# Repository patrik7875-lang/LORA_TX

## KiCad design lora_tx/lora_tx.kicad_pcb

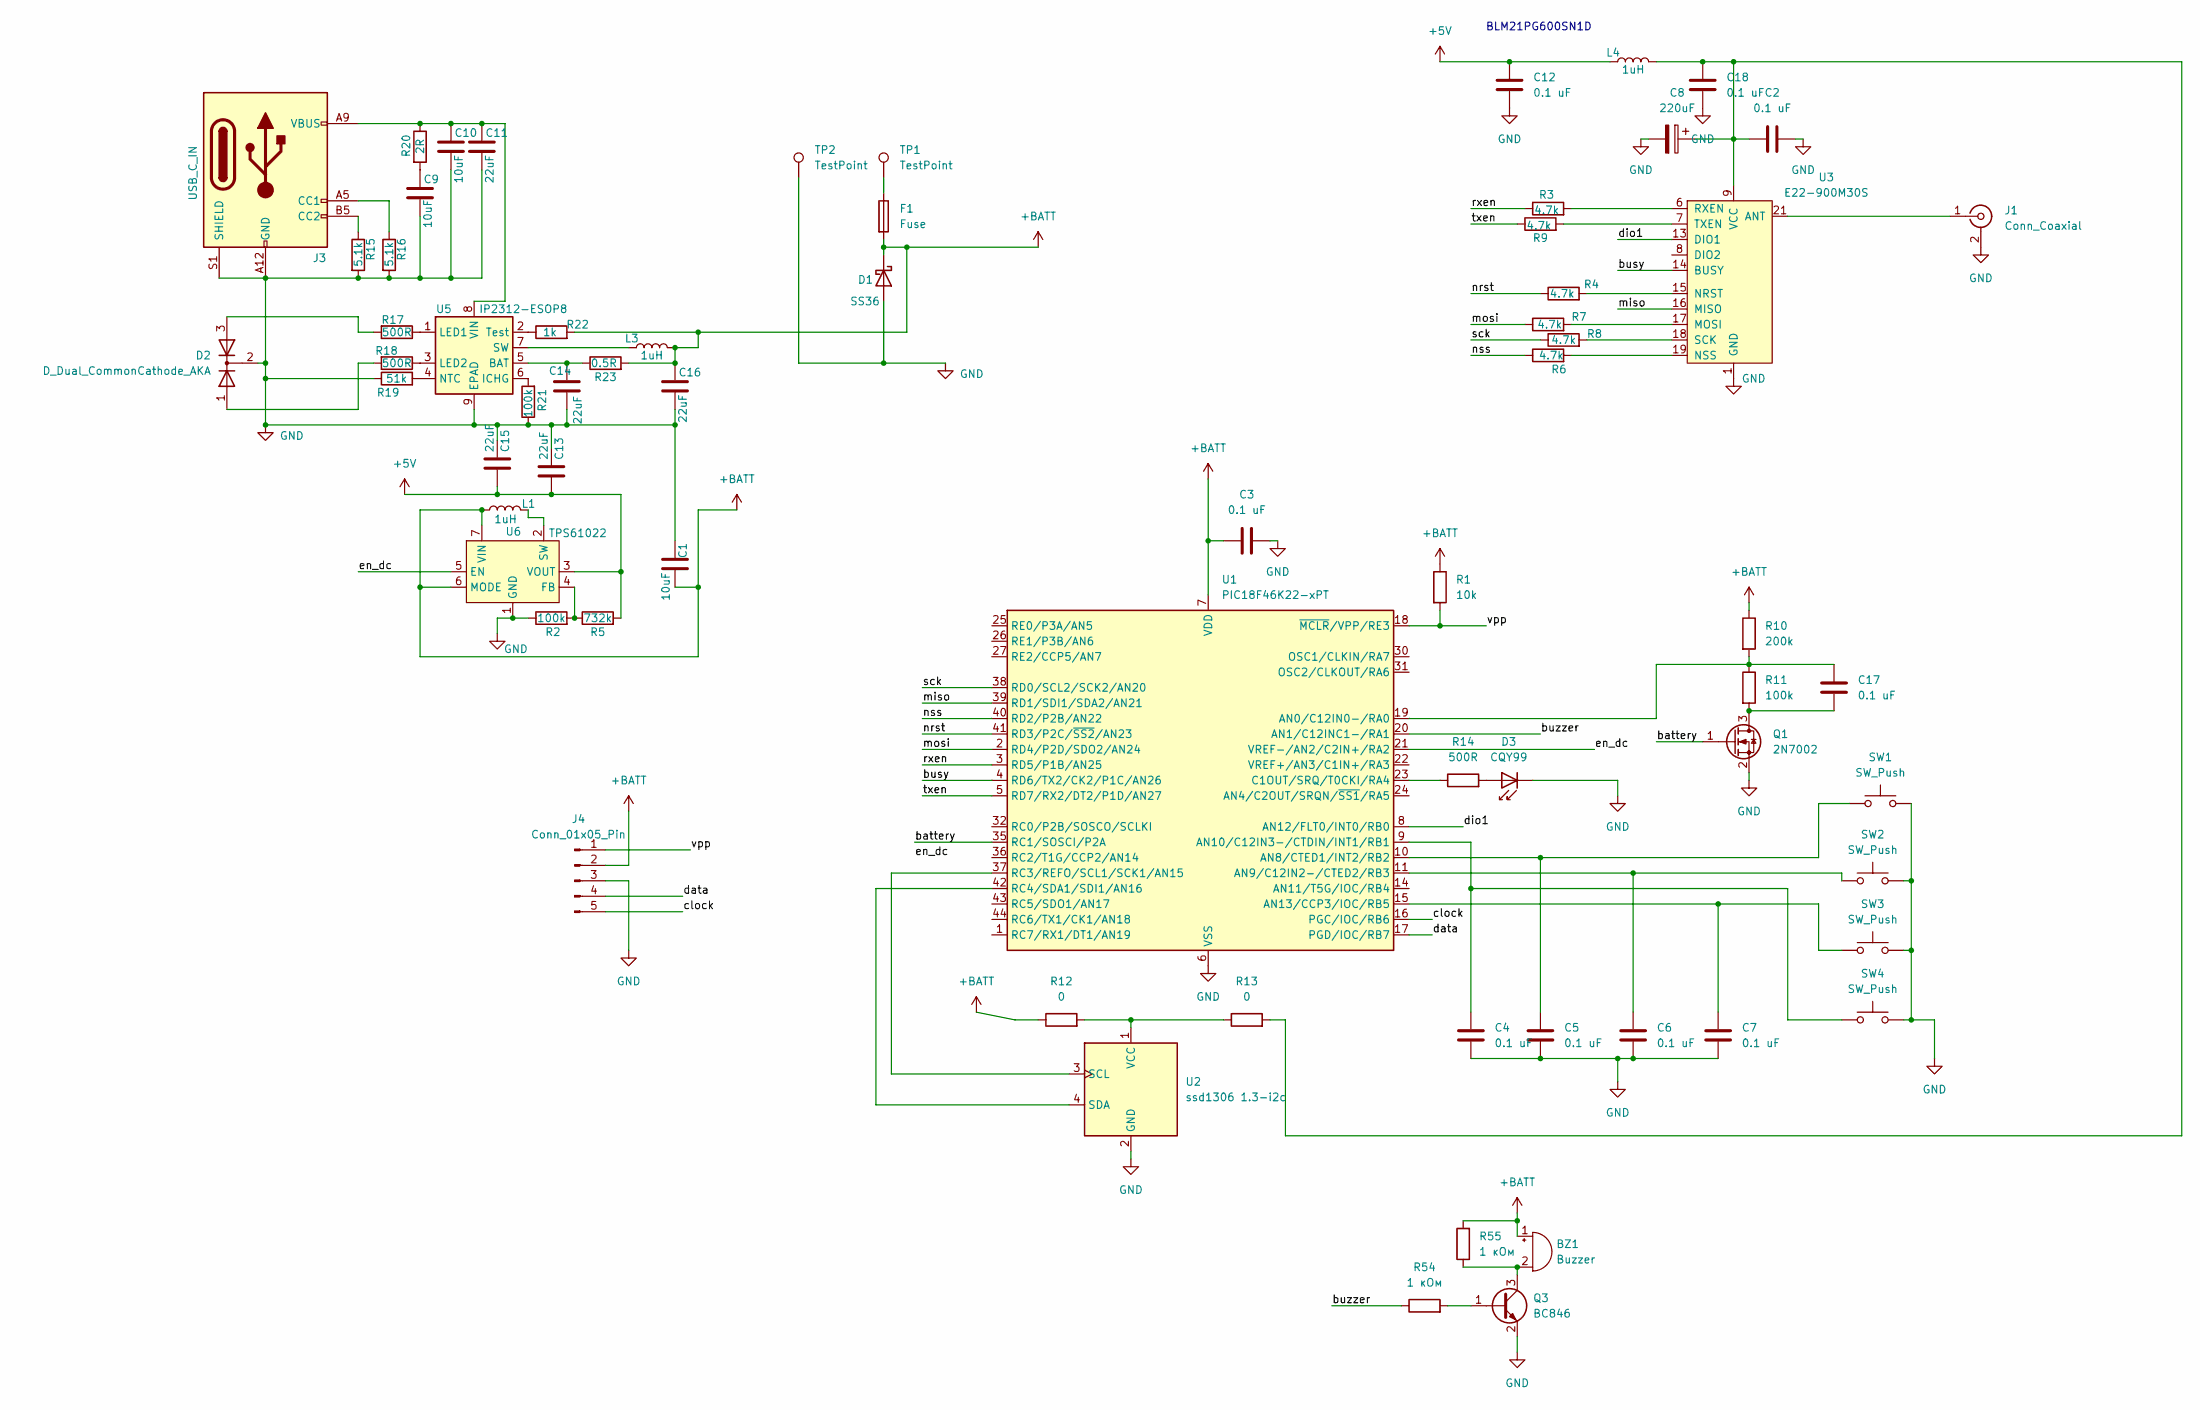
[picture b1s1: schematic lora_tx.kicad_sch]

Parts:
BZ1: Buzzer; Buzzer_Murata_PKMCS0909E
C1, C9, C10: 10uF; C_0805_2012Metric_Pad1.18x1.45mm_HandSolder
C2, C3, C12, C17, C18: 0.1 uF; LED_0805_2012Metric
C4, C5, C6, C7: 0.1 uF; C_0805_2012Metric
C8: 220uF; CP_EIA-7343-31_Kemet-D
C11, C13, C14, C15, C16: 22uF; C_1206_3216Metric
D1: SS36; D_SMA
D2: D_Dual_CommonCathode_AKA; LED_D3.0mm-3
D3: CQY99; LED_D1.8mm_W1.8mm_H2.4mm_Horizontal_O1.27mm_Z8.2mm
F1: Fuse; Fuse_1210_3225Metric
J1: Conn_Coaxial; SMA_Molex_73251-1153_EdgeMount_Horizontal
J3: USB_C_IN; USB_C_Receptacle_GCT_USB4125-xx-x_6P_TopMnt_Horizontal
J4: Conn_01x05_Pin; PinHeader_1x05_P2.54mm_Vertical
L1, L3: 1uH; L_Chilisin_BMRA00050520
L4: 1uH; L_0805_2012Metric
Q1: 2N7002; SOT-23
Q3: BC846; SOT-23
R1: 10k; R_0805_2012Metric
R2, R21: 100k; R_0805_2012Metric_Pad1.20x1.40mm_HandSolder
R3, R4, R6, R7, R8, R9: 4.7k; R_0805_2012Metric
R5: 732k; R_0805_2012Metric_Pad1.20x1.40mm_HandSolder
R10: 200k; R_0805_2012Metric
R11: 100k; R_0805_2012Metric
R12, R13: 0; R_1206_3216Metric
R14: 500R; R_0805_2012Metric
R15, R16: 5.1k; R_0805_2012Metric_Pad1.20x1.40mm_HandSolder
R17, R18: 500R; R_0805_2012Metric_Pad1.20x1.40mm_HandSolder
R19: 51k; R_0805_2012Metric_Pad1.20x1.40mm_HandSolder
R20: 2R; R_0805_2012Metric_Pad1.20x1.40mm_HandSolder
R22: 1k; R_0805_2012Metric_Pad1.20x1.40mm_HandSolder
R23: 0.5R; R_0805_2012Metric_Pad1.20x1.40mm_HandSolder
R54, R55: 1 кОм; R_0805_2012Metric
SW1, SW2, SW3, SW4: SW_Push; SW_Tactile_SPST_Angled_PTS645Vx39-2LFS
TP1, TP2: TestPoint; TestPoint_Keystone_5015_Micro_Mini
U1: PIC18F46K22-xPT; TQFP-44_10x10mm_P0.8mm
U2: ssd1306 1.3-i2c; Display_128x64_1,3_I2C_,no_drill
U3: E22-900M30S; e22-900m30s-handsoldering; LCSC# C411294
U5: IP2312-ESOP8; SOIC-8-1EP_3.9x4.9mm_P1.27mm_EP2.41x3.3mm_ThermalVias
U6: TPS61022; Texas_RWU0007A_VQFN-7_2x2mm_P0.5mm

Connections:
+5V: C12.1, C13.2, C15.2, L4.1, R5.2, U6.3 (VOUT)
+BATT: BZ1.1 (+), C1.1, C3.2, C16.1, D1.1 (K), F1.2, J4.2, L1.1, L3.2, R1.1, R10.1, R12.1, R22.2, R23.2, R55.2, U1.7 (VDD), U1.28 (VDD), U6.6 (MODE), U6.7 (VIN)
/battery: Q1.1 (G), U1.35 (RC1/SOSCI/P2A)
/busy: U1.4 (RD6/TX2/CK2/P1C/AN26), U3.14 (BUSY)
/buzzer: R54.1, U1.20 (AN1/C12INC1-/RA1)
/clock: J4.5, U1.16 (PGC/IOC/RB6)
/data: J4.4, U1.17 (PGD/IOC/RB7)
/dio1: U1.8 (AN12/FLT0/INT0/RB0), U3.13 (DIO1)
/en_dc: U1.21 (VREF-/AN2/C2IN+/RA2), U6.5 (EN)
/miso: U1.39 (RD1/SDI1/SDA2/AN21), U3.16 (MISO)
/mosi: R7.1, U1.2 (RD4/P2D/SDO2/AN24)
/nrst: R4.1, U1.41 (RD3/P2C/~SS2/AN23)
/nss: R6.1, U1.40 (RD2/P2B/AN22)
/rxen: R3.1, U1.3 (RD5/P1B/AN25)
/sck: R8.1, U1.38 (RD0/SCL2/SCK2/AN20)
/txen: R9.1, U1.5 (RD7/RX2/DT2/P1D/AN27)
/vpp: J4.1, R1.2, U1.18 (~MCLR/VPP/RE3)
GND: C1.2, C2.1, C3.1, C4.2, C5.1, C6.2, C7.2, C8.2, C9.2, C10.2, C11.2, C12.2, C13.1, C14.2, C15.1, C16.2, C18.2, D1.2 (A), D2.2 (K), D3.1 (K), J1.2 (Ext), J3.A12 (GND), J3.B12 (GND), J3.S1 (SHIELD), J4.3, Q1.2 (S), Q3.2 (E), R2.1, R15.2, R16.2, R19.1, R21.1, SW1.1, SW2.1, SW3.1, SW4.1, TP2.1 (1_1), U1.6 (VSS), U1.29 (VSS), U2.2 (GND), U3.1 (GND), U3.2 (GND), U3.3 (GND), U3.4 (GND), U3.5 (GND), U3.11 (GND), U3.12 (GND), U3.20 (GND), U3.22 (GND), U5.9 (EPAD), U6.1 (GND)
unnamed: BZ1.2 (-), Q3.3 (C), R55.1
unnamed: C9.1, R20.2
unnamed: D2.1 (A), R18.2
unnamed: D2.3 (A), R17.2
unnamed: D3.2 (A), R14.2
unnamed: F1.1, TP1.1 (1_1)
unnamed: J1.1 (In), U3.21 (ANT)
unnamed: J3.A5 (CC1), R16.1
unnamed: J3.B5 (CC2), R15.1
unnamed: C17.2, Q1.3 (D), R11.2
unnamed: Q3.1 (B), R54.2
unnamed: C17.1, R10.2, R11.1, U1.19 (AN0/C12IN0-/RA0)
unnamed: C5.2, SW1.2, U1.10 (AN8/CTED1/INT2/RB2)
unnamed: C6.1, SW2.2, U1.11 (AN9/C12IN2-/CTED2/RB3)
unnamed: C4.1, SW4.2, U1.9 (AN10/C12IN3-/CTDIN/INT1/RB1)
unnamed: C7.1, SW3.2, U1.15 (AN13/CCP3/IOC/RB5)
unnamed: R14.1, U1.23 (C1OUT/SRQ/T0CKI/RA4)
unnamed: U1.37 (RC3/REFO/SCL1/SCK1/AN15), U2.3 (SCL)
unnamed: U1.42 (RC4/SDA1/SDI1/AN16), U2.4 (SDA)
unnamed: R12.2, R13.1, U2.1 (VCC)
unnamed: R7.2, U3.17 (MOSI)
unnamed: R4.2, U3.15 (NRST)
unnamed: R6.2, U3.19 (NSS)
unnamed: R3.2, U3.6 (RXEN)
unnamed: R8.2, U3.18 (SCK)
unnamed: R9.2, U3.7 (TXEN)
unnamed: C14.1, R23.1, U5.5 (BAT)
unnamed: R21.2, U5.6 (ICHG)
unnamed: R17.1, U5.1 (LED1)
unnamed: R18.1, U5.3 (LED2)
unnamed: R19.2, U5.4 (NTC)
unnamed: L3.1, U5.7 (SW)
unnamed: R22.1, U5.2 (Test)
unnamed: C10.1, C11.1, J3.A9 (VBUS), J3.B9 (VBUS), R20.1, U5.8 (VIN)
unnamed: R2.2, R5.1, U6.4 (FB)
unnamed: L1.2, U6.2 (SW)
VCC: C2.2, C8.1, C18.1, L4.2, R13.2, U3.9 (VCC), U3.10 (VCC)

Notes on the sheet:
BLM21PG600SN1D

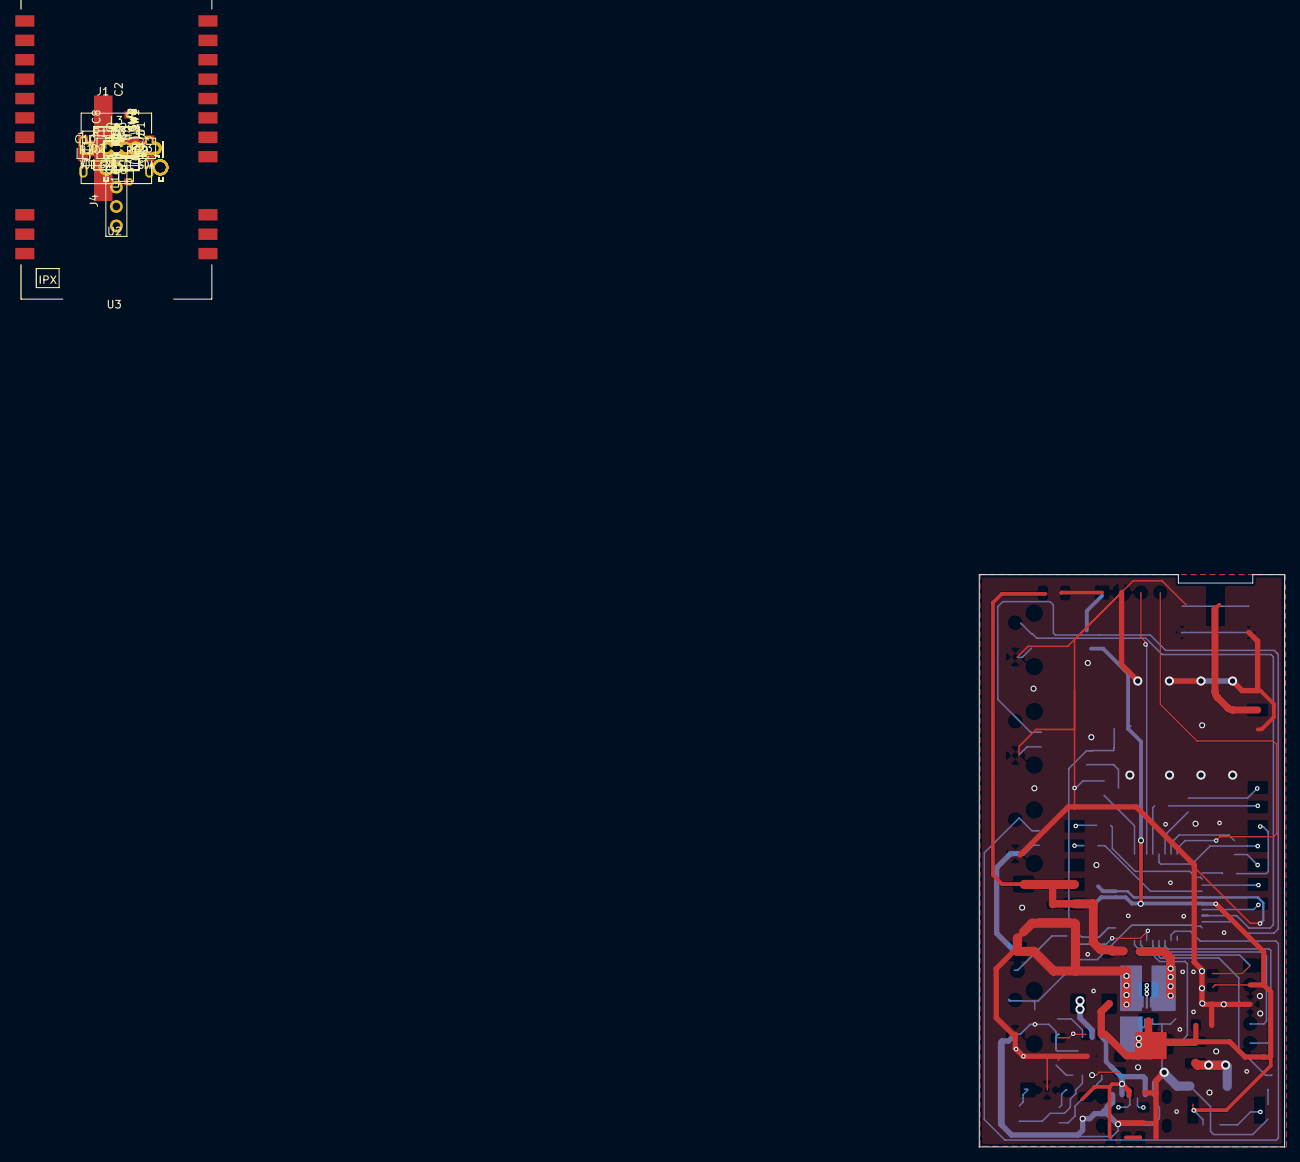
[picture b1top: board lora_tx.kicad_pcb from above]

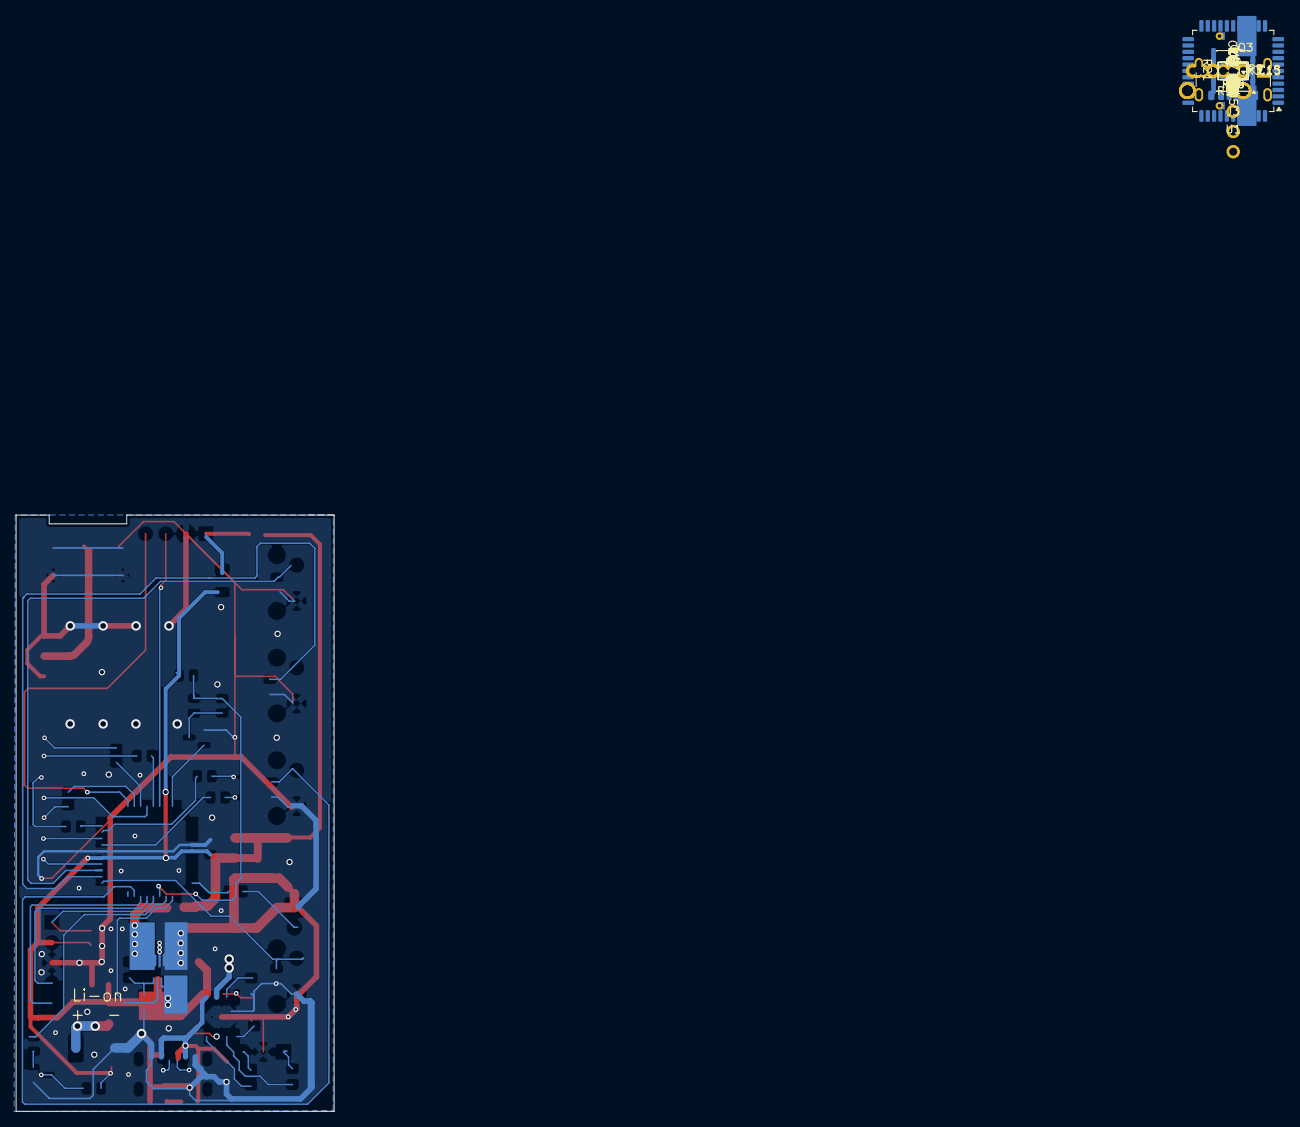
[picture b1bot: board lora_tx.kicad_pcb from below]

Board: 2 copper layers, 40.0 x 75.0 mm, 67 parts (35 on the bottom side), 55 nets.
